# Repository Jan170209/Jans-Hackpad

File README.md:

# Jans-Hackpad

A macropad with 6 keys and a knob to control volume etc. The little cutout at the top left is window to see the microcontroller.

# BOM
- 1x PCB
- 6x Cherry MX Switches
- 6x Keycaps
- 1x EC11 Rotary encoder
- 1x Seeed XIAO RP2040
- 4x M3x5x4 heatset inserts
- 4x M3x16mm screw

# Images

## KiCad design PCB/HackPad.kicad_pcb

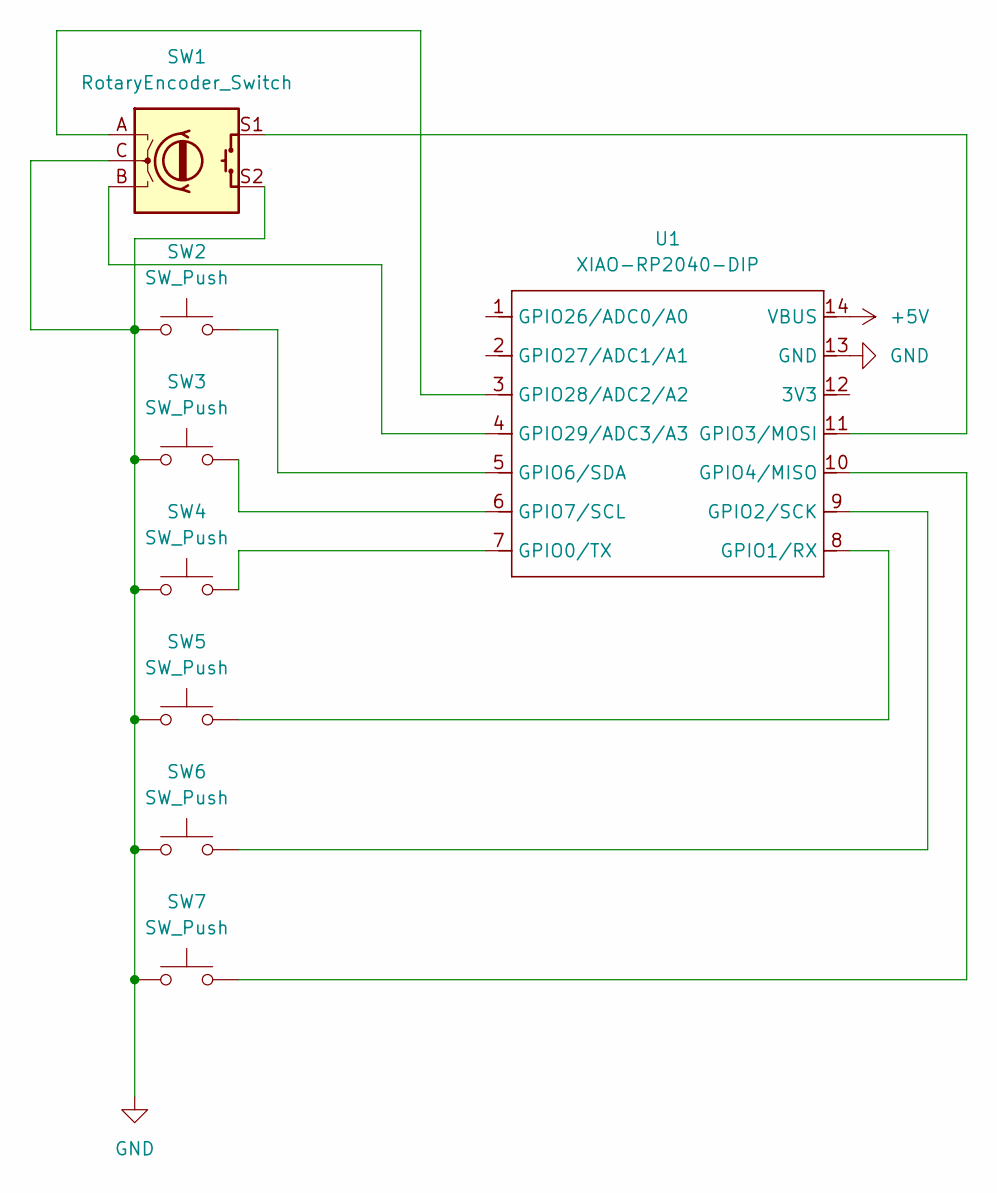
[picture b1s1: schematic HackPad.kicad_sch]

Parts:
SW1: RotaryEncoder_Switch; RotaryEncoder_Alps_EC11E-Switch_Vertical_H20mm
SW2, SW3, SW4, SW5, SW6, SW7: SW_Push; SW_Cherry_MX_1.00u_PCB
U1: XIAO-RP2040-DIP

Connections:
+5V: U1.14 (VBUS)
GND: SW1.C, SW1.S2, SW2.1, SW3.1, SW4.1, SW5.1, SW6.1, SW7.1, U1.13 (GND)
unnamed: SW4.2, U1.7 (GPIO0/TX)
unnamed: SW5.2, U1.8 (GPIO1/RX)
unnamed: SW6.2, U1.9 (GPIO2/SCK)
unnamed: SW1.S1, U1.11 (GPIO3/MOSI)
unnamed: SW7.2, U1.10 (GPIO4/MISO)
unnamed: SW2.2, U1.5 (GPIO6/SDA)
unnamed: SW3.2, U1.6 (GPIO7/SCL)
unnamed: SW1.A, U1.3 (GPIO28/ADC2/A2)
unnamed: SW1.B, U1.4 (GPIO29/ADC3/A3)

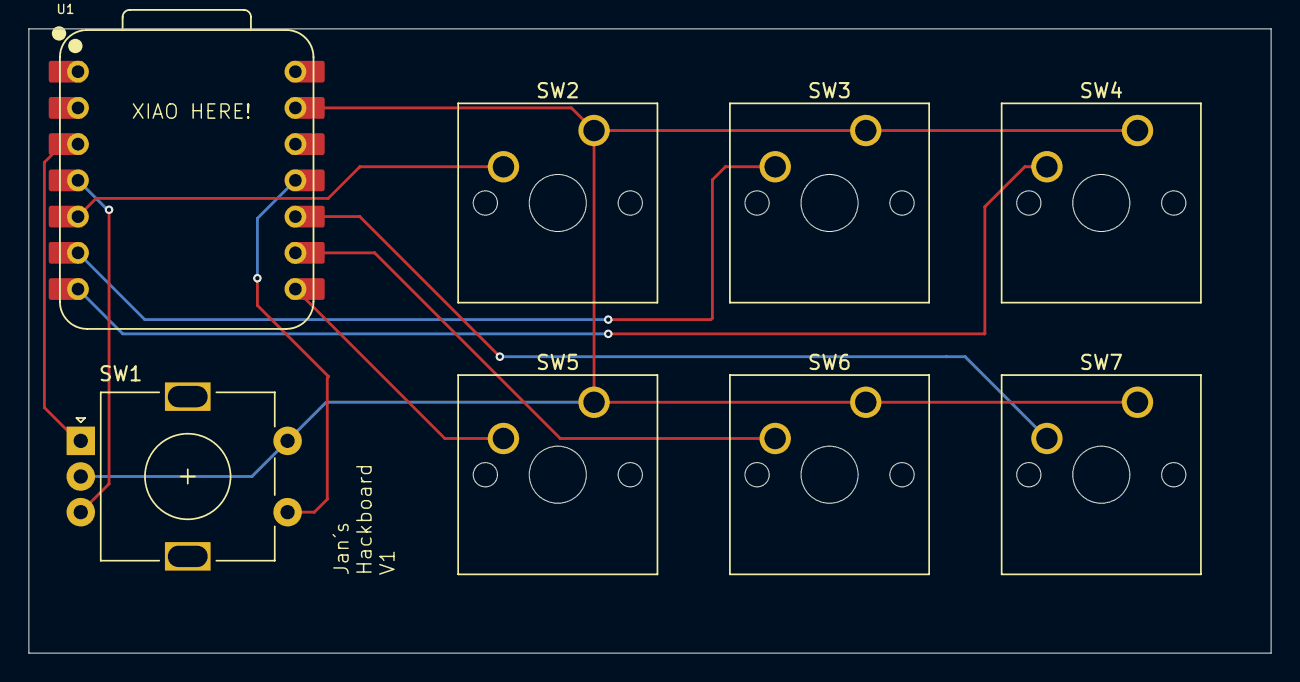
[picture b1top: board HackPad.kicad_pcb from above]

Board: 2 copper layers, 87.1 x 43.8 mm, 8 parts (0 on the bottom side), 10 nets.

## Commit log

2026-01-19 Create temp
2026-02-06 Create production temp
